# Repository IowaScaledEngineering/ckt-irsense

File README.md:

This is the software library, example applications, and hardware design files for the Iowa Scaled Engineering CKT-IRSENSE Reflective Infrared Proximity Sensor

The product can be found at:
http://www.iascaled.com/store/CKT-IRSENSE

Hardware use documentation (the manual) can be found in the /doc/ directory.

Like all public Iowa Scaled Engineering designs, the CKT-IRSENSE is both open hardware and open source software.  Please refer to the hardware and software license files in this repository for details.

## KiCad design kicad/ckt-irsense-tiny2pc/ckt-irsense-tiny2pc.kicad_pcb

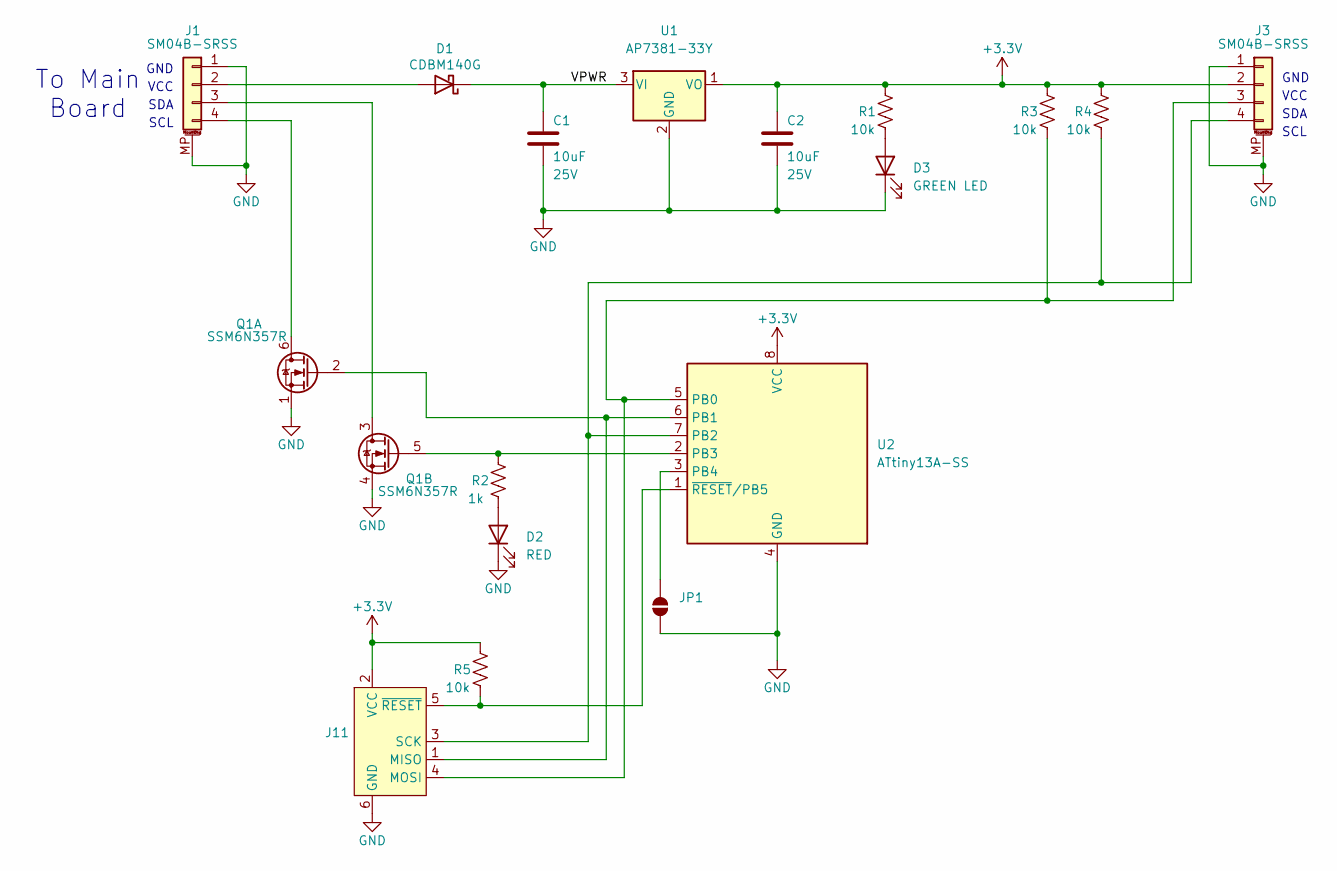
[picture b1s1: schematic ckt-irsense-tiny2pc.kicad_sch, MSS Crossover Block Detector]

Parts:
C1, C2: 10uF; C_0805_2012Metric; Voltage 25V
D1: CDBM140G; SOD-123T
D2: RED; LED_0805_2012Metric
D3: GREEN LED; LED_0805_2012Metric
J1, J3: SM04B-SRSS; JST_SH_SM04B-SRSS-TB_1x04-1MP_P1.00mm_Horizontal
J11: Conn_AVR_TagConnect_TC2030; Tag-Connect_TC2030-IDC-NL_2x03_P1.27mm_Vertical
JP1: SolderJumper_2_Open; SolderJumper-2_P1.3mm_Open_RoundedPad1.0x1.5mm
Q1: SSM6N357R; TSOP6F
R1, R3, R4, R5: 10k; R_0805_2012Metric
R2: 1k; R_0805_2012Metric
U1: AP7381-33Y; SOT-89-3
U2: ATtiny13A-SS; ATMEL_SO8_DUAL

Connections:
+3.3V: C2.1, J3.2, J11.2 (VCC), R1.2, R3.2, R4.2, R5.2, U1.1 (VO), U2.8 (VCC)
/VPWR: C1.1, D1.1 (K), U1.3 (VI)
GND: C1.2, C2.2, D2.1 (K), D3.1 (K), J1.1, J1.MP (MountPin), J3.1, J3.MP (MountPin), J11.6 (GND), JP1.1 (A), Q1.1 (S), Q1.4 (S), U1.2 (GND), U2.4 (GND)
unnamed: D1.2 (A), J1.2
unnamed: D2.2 (A), R2.1
unnamed: D3.2 (A), R1.1
unnamed: J1.3, Q1.3 (D)
unnamed: J1.4, Q1.6 (D)
unnamed: J11.1 (MISO), Q1.2 (G), U2.6 (PB1)
unnamed: J3.3, J11.4 (MOSI), R3.1, U2.5 (PB0)
unnamed: J3.4, J11.3 (SCK), R4.1, U2.7 (PB2)
unnamed: J11.5 (~RESET), R5.1, U2.1 (~RESET/PB5)
unnamed: JP1.2 (B), U2.3 (PB4)
unnamed: Q1.5 (G), R2.2, U2.2 (PB3)

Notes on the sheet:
GND
VCC
SCL
SDA
To Main Board

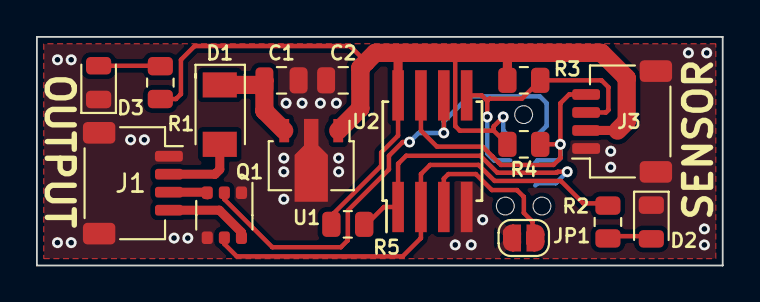
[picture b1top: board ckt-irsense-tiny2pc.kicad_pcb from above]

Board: 2 copper layers, 38.1 x 12.7 mm, 17 parts (1 on the bottom side), 14 nets.

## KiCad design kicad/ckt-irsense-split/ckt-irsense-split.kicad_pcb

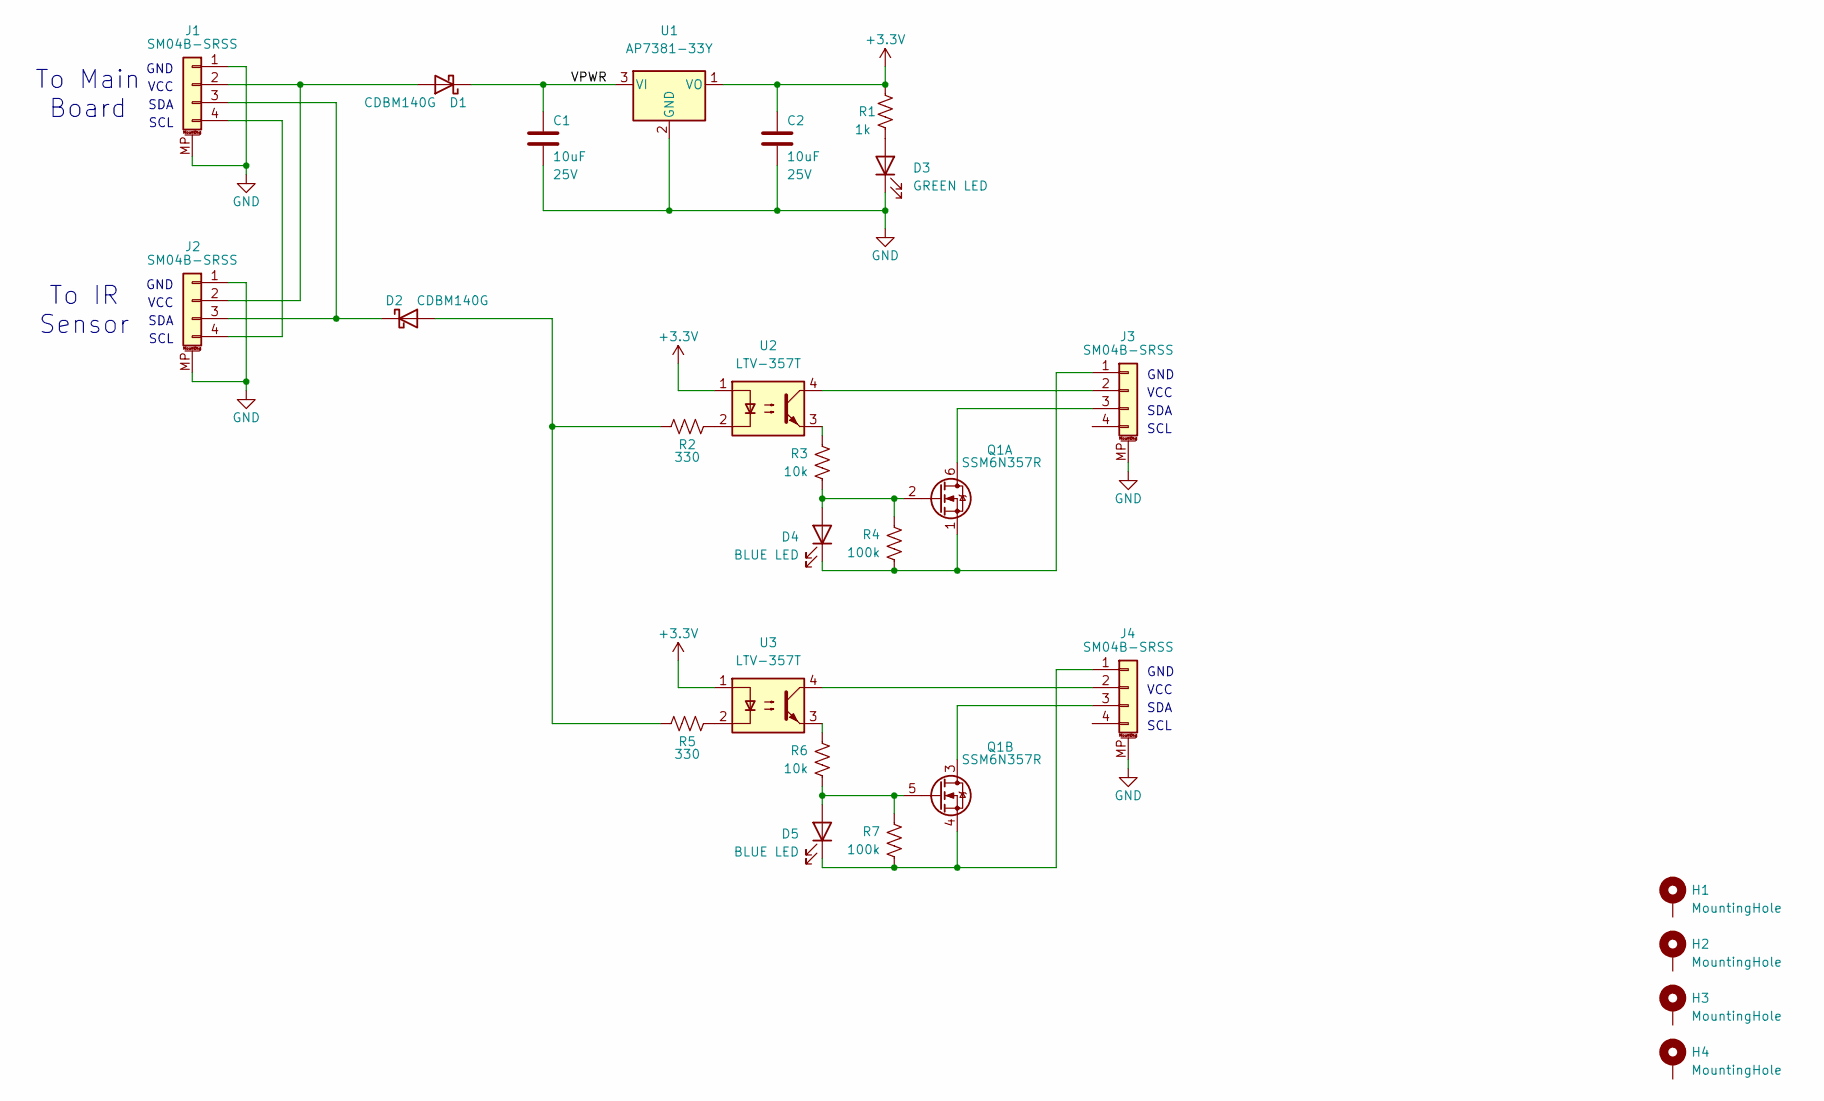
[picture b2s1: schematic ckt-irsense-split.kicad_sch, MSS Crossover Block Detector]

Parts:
C1, C2: 10uF; C_0805_2012Metric; Voltage 25V
D1, D2: CDBM140G; SOD-123T
D3: GREEN LED; LED_0805_2012Metric
D4, D5: BLUE LED; LED_0805_2012Metric
H1, H2, H3, H4: MountingHole; MountingHole_3.2mm_M3_Pad
J1, J2, J3, J4: SM04B-SRSS; JST_SH_SM04B-SRSS-TB_1x04-1MP_P1.00mm_Horizontal
Q1: SSM6N357R; TSOP6F
R1: 1k; R_0805_2012Metric
R2, R5: 330; R_0805_2012Metric
R3, R6: 10k; R_0805_2012Metric
R4, R7: 100k; R_0805_2012Metric
U1: AP7381-33Y; SOT-89-3
U2, U3: LTV-357T; SO-4_4.4x3.6mm_P2.54mm

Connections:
+3.3V: C2.1, R1.2, U1.1 (VO), U2.1, U3.1
/VPWR: C1.1, D1.1 (K), U1.3 (VI)
GND: C1.2, C2.2, D3.1 (K), J1.1, J1.MP (MountPin), J2.1, J2.MP (MountPin), J3.MP (MountPin), J4.MP (MountPin), U1.2 (GND)
unnamed: D1.2 (A), J1.2, J2.2
unnamed: D2.2 (A), R2.2, R5.2
unnamed: D2.1 (K), J1.3, J2.3
unnamed: D3.2 (A), R1.1
unnamed: D4.2 (A), Q1.2 (G), R3.1, R4.2
unnamed: D4.1 (K), J3.1, Q1.1 (S), R4.1
unnamed: D5.2 (A), Q1.5 (G), R6.1, R7.2
unnamed: D5.1 (K), J4.1, Q1.4 (S), R7.1
unnamed: J1.4, J2.4
unnamed: J3.2, U2.4
unnamed: J3.3, Q1.6 (D)
unnamed: J4.2, U3.4
unnamed: J4.3, Q1.3 (D)
unnamed: R2.1, U2.2
unnamed: R3.2, U2.3
unnamed: R5.1, U3.2
unnamed: R6.2, U3.3

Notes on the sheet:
SDA
GND
To IR Sensor
VCC
SCL
To Main Board

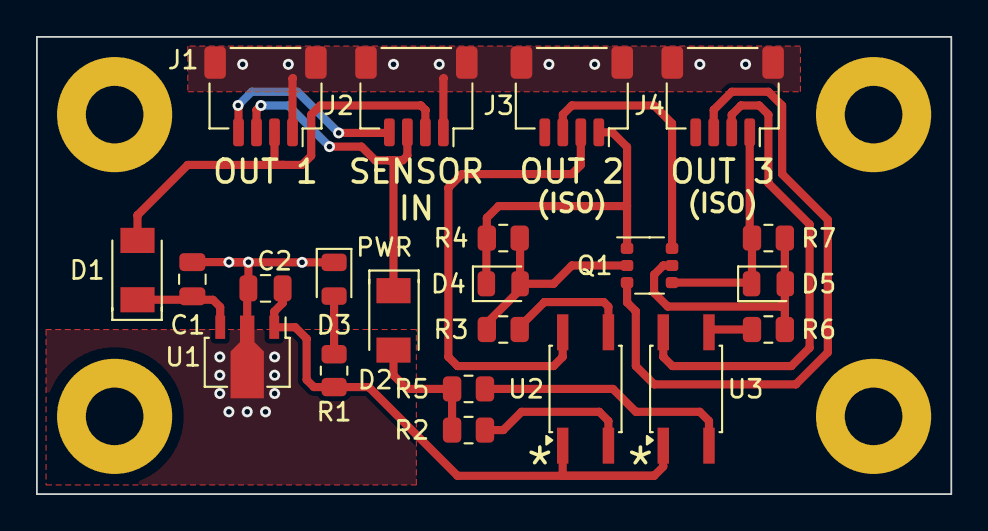
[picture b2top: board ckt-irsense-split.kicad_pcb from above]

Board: 2 copper layers, 50.8 x 25.4 mm, 26 parts (0 on the bottom side), 20 nets.

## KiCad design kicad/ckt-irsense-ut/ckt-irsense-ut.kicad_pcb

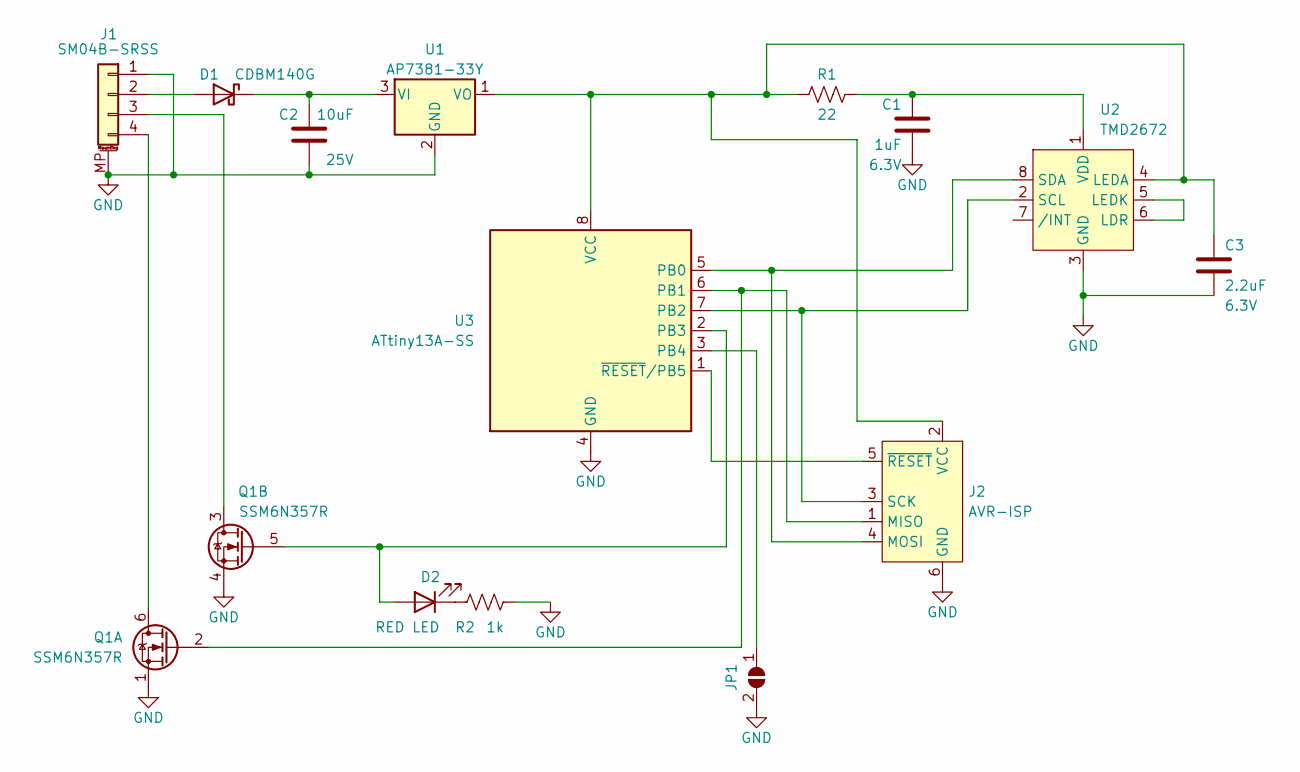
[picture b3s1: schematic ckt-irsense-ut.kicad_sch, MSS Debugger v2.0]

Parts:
C1: 1uF; C_0805_2012Metric; Voltage 6.3V
C2: 10uF; C_0805_2012Metric; Voltage 25V
C3: 2.2uF; C_0805_2012Metric; Voltage 6.3V
D1: CDBM140G; SOD-123T
D2: RED LED; LED_0805_2012Metric
J1: SM04B-SRSS; JST_SH_SM04B-SRSS-TB_1x04-1MP_P1.00mm_Horizontal
J2: AVR-ISP; Tag-Connect_TC2030-IDC-NL_2x03_P1.27mm_Vertical
JP1: SolderJumper_2_Open; SolderJumper-2_P1.3mm_Open_RoundedPad1.0x1.5mm
Q1: SSM6N357R; TSOP6F
R1: 22; R_0805_2012Metric
R2: 1k; R_0805_2012Metric
U1: AP7381-33Y; SOT-89-3
U2: TMD2672
U3: ATtiny13A-SS; SOIC-8_3.9x4.9mm_P1.27mm

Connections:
GND: C1.2, C2.2, C3.2, J1.1, J1.MP (MountPin), J2.6 (GND), JP1.2 (B), Q1.1 (S), Q1.4 (S), R2.1, U1.2 (GND), U2.3 (GND), U3.4 (GND)
unnamed: C1.1, R1.1, U2.1 (VDD)
unnamed: C2.1, D1.1 (K), U1.3 (VI)
unnamed: C3.1, J2.2 (VCC), R1.2, U1.1 (VO), U2.4 (LEDA), U3.8 (VCC)
unnamed: D1.2 (A), J1.2
unnamed: D2.1 (K), R2.2
unnamed: D2.2 (A), Q1.5 (G), U3.2 (PB3)
unnamed: J1.3, Q1.3 (D)
unnamed: J1.4, Q1.6 (D)
unnamed: J2.1 (MISO), Q1.2 (G), U3.6 (PB1)
unnamed: J2.3 (SCK), U2.2 (SCL), U3.7 (PB2)
unnamed: J2.4 (MOSI), U2.8 (SDA), U3.5 (PB0)
unnamed: J2.5 (~RESET), U3.1 (~RESET/PB5)
unnamed: JP1.1 (A), U3.3 (PB4)
unnamed: U2.5 (LEDK), U2.6 (LDR)

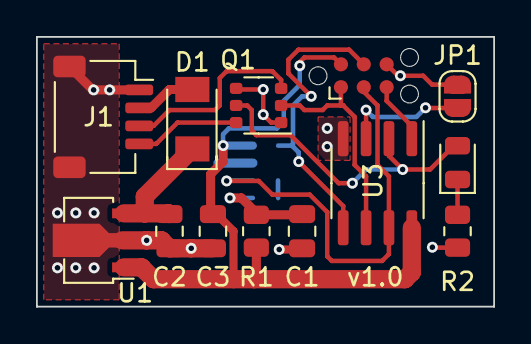
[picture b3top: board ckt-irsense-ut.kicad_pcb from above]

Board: 2 copper layers, 25.4 x 15.0 mm, 14 parts (1 on the bottom side), 15 nets.

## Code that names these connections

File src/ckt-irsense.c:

/*************************************************************************
Title:    IR reflective sensor v3.1
Authors:  Michael Petersen <railfan@drgw.net>
          Nathan D. Holmes <maverick@drgw.net>
File:     $Id: $
License:  GNU General Public License v3

LICENSE:
    Copyright (C) 2014 Michael Petersen & Nathan Holmes

    This program is free software; you can redistribute it and/or modify
    it under the terms of the GNU General Public License as published by
    the Free Software Foundation; either version 3 of the License, or
    any later version.

    This program is distributed in the hope that it will be useful,
    but WITHOUT ANY WARRANTY; without even the implied warranty of
    MERCHANTABILITY or FITNESS FOR A PARTICULAR PURPOSE.  See the
    GNU General Public License for more details.

*************************************************************************/

#include <stdlib.h>
#include <stdbool.h>
#include <avr/io.h>
#include <avr/interrupt.h>
#include <avr/wdt.h>
#include <util/delay.h>
#include <avr/eeprom.h>


#define   TMD267x1_ADDR   0x39
#define   INFO_ADDR       0x20

#define   PROXIMITY_THRESHOLD_DEFAULT     0x300
#define   SENSOR_ERROR_THRESHOLD  0
#define   PPULSE_DEFAULT          8

#define   ON_DEBOUNCE_DEFAULT   1

#define   SDA   PB0
#define   SCL   PB2

static inline void sda_low() { DDRB |= _BV(SDA); PORTB &= ~_BV(SDA); _delay_us(10); }
static inline void sda_high() { DDRB &= ~_BV(SDA); PORTB |= _BV(SDA); _delay_us(10); }
static inline void scl_low() { PORTB &= ~_BV(SCL); _delay_us(10); }
static inline void scl_high() { PORTB |= _BV(SCL); _delay_us(10); }

volatile uint8_t ticks;
volatile uint8_t decisecs = 0;

void initialize100HzTimer(void)
{
	// Set up timer 0 for 100Hz interrupts
	TCNT0 = 0;
	OCR0A = 94;  // 9.6MHz / 1024 / 94 = 100Hz
	ticks = 0;
	decisecs = 0;
	TCCR0A = _BV(WGM01);
	TCCR0B = _BV(CS02) | _BV(CS00);  // 1024 prescaler
	TIMSK0 |= _BV(OCIE0A);
}

ISR(TIM0_COMPA_vect)
{
	if (++ticks >= 10)
	{
		ticks = 0;
		decisecs++;
	}
}

void i2cStart(void)
{
	scl_high();
	sda_low();
	scl_low();
	sda_high();
}

void i2cStop(void)
{
	scl_low();
	sda_low();
	scl_high();
	sda_high();
}

uint8_t i2cWriteByte(uint8_t byte)
{
	uint8_t i = 0x80, ack;

	do
	{
		if(byte & i)
		{
			sda_high();
		}
		else
		{
			sda_low();
		}
		
		scl_high();
		scl_low();
		
		i >>= 1;
	} while(i);

	sda_high();  // Release SDA
	
	scl_high();
	if(PINB & _BV(SDA))
		ack = 0;
	else
		ack = 1;
	scl_low();

	return ack;
}

uint8_t i2cReadByte(uint8_t ack)
{
	uint8_t i, data = 0;

	for(i=0; i<8; i++)
	{
		data = data << 1;
		scl_high();
		if(PINB & _BV(SDA))
			data |= 0x01;
		scl_low();
	}
	
	if(ack)
		sda_low();
	scl_high();
	scl_low();
	sda_high();

	return data;
}

uint8_t writeByte(uint8_t addr, uint8_t cmd, uint16_t writeVal)
{
	uint8_t ack;
	
	i2cStart();
	
	i2cWriteByte(addr << 1);
	i2cWriteByte(cmd);
	ack = i2cWriteByte(writeVal);

	i2cStop();

	return ack;
}

uint8_t readWord(uint8_t addr, uint8_t cmd, uint16_t* data)
{
	uint8_t ack = 1;
	*data = 0xFFFF;
	
	i2cStart();
	
	ack &= i2cWriteByte(addr << 1);
	ack &= i2cWriteByte(cmd);

	i2cStart();

	ack &= i2cWriteByte((addr << 1) | 0x01);
	*data = i2cReadByte(1);
	*data |= ((uint16_t)i2cReadByte(0) << 8);
	
	i2cStop();

	return ack;
}

void init(void)
{
	MCUSR = 0;
	wdt_reset();
	wdt_enable(WDTO_250MS);
	wdt_reset();

	// Configure ADC
	ADMUX = 0x02;  // ref = VCC, right-justified, input = PB4 (ADC2)
	ADCSRA = 0x87; // ADC enabled, prescaler = 128
	DIDR0 = _BV(ADC2D);  // Disable ADC2 digital input buffer
	
	PORTB = _BV(SCL) | _BV(PB1);  // All outputs low except SCL and PB1
	DDRB |= _BV(PB1) | _BV(SCL) | _BV(PB3);
	
#ifndef TWOPIECE
	// Enable internal pull-up on ADJ pin
	DDRB &= ~_BV(PB4);
	PORTB |= _BV(PB4);
#endif
}

#define TMD26711_ID_VALUE 0x20
#define TMD26713_ID_VALUE 0x29
#define TMD26721_ID_VALUE 0x32
#define TMD26723_ID_VALUE 0x38

void initializeTMD267x1()
{
	uint16_t i=0;
	uint8_t isTMD2671x = 0;
	
	// Initialize TMD267x1 (bit 0x80 set to indicate command)
	writeByte(TMD267x1_ADDR, 0x80|0x00, 0x00);   // Start with everything disabled
	writeByte(TMD267x1_ADDR, 0x80|0x01, 0xFF);   // Minimum ATIME
	writeByte(TMD267x1_ADDR, 0x80|0x02, 0xFF);   // Maximum integration time
	writeByte(TMD267x1_ADDR, 0x80|0x03, 0xFF);   // Minimum wait time

	if (readWord(TMD267x1_ADDR, 0x80|0x20|0x12, &i))
	{
		if ((i & 0xFF) < TMD26721_ID_VALUE) // Also applies for TMD277xx, same IDs
			isTMD2671x = 1;
	}
	
	// Note: IRQ not currently used
	writeByte(TMD267x1_ADDR, 0x80|0x08, 0x00);   // Set interrupt low threshold to 0x0000
	writeByte(TMD267x1_ADDR, 0x80|0x09, 0x00);
	writeByte(TMD267x1_ADDR, 0x80|0x0A, 0x00);   // Set interrupt low threshold to 0x0300
	writeByte(TMD267x1_ADDR, 0x80|0x0B, 0x03);
	writeByte(TMD267x1_ADDR, 0x80|0x0C, 0x10);   // Single out-of-range cycle triggers interrupt

	writeByte(TMD267x1_ADDR, 0x80|0x0D, 0x00);   // Long wait disabled
	writeByte(TMD267x1_ADDR, 0x80|0x0E, PPULSE_DEFAULT); // Pulse count

	writeByte(TMD267x1_ADDR, 0x80|0x0F, isTMD2671x?0x20:0x28);   // 100% LED drive strength, Use channel 1 diode (ch 1 seems less sensitive to fluorescent light) - TMD26711
	writeByte(TMD267x1_ADDR, 0x80|0x00, 0x27);   // Power ON, Enable proximity, Enable proximity interrupt (not used currently)
}

void setOutputs(bool detect)
{
#ifdef DOUBLEOUTPUT
	// In this mode, both outputs are active if detection, inactive otherwise
	// Useful for MSS-type setups
	if(detect)
	{
		PORTB |= _BV(PB3) | _BV(PB1);
	}
	else
	{
		PORTB &= ~(_BV(PB3) | _BV(PB1));
	}

#elif defined PULSE_OUTPUT
	static bool prev_detect = false;
	if (prev_detect != detect)
	{
		if (prev_detect)
			PORTB |= _BV(PB1);
		else
			PORTB |= _BV(PB3);
	} else {
		PORTB &= ~(_BV(PB3) | _BV(PB1));
	}
	prev_detect = detect;

	
#else
	if(detect)
	{
		PORTB |= _BV(PB3);
		PORTB &= ~_BV(PB1);
	}
	else
	{
		PORTB &= ~_BV(PB3);
		PORTB |= _BV(PB1);
	}
#endif

}

int main(void)
{
#ifdef TWOPIECE
	//  Two Piece Specific Setup
	uint16_t proximity_threshold = PROXIMITY_THRESHOLD_DEFAULT;
	uint16_t count = 0;  // 256 decisecs * 60 (long delay mode) = 15360 max count
	int16_t on_debounce, off_debounce;  // Signed so the math for off_debounce doesn't wrap
#else
	//  One Piece Specific Setup
	uint16_t proximity_threshold = (eeprom_read_byte((const uint8_t *)0x00) << 8) + eeprom_read_byte((const uint8_t *)0x01);
	if(0xFFFF == proximity_threshold)
		proximity_threshold = PROXIMITY_THRESHOLD_DEFAULT;
	uint8_t count = 0;
	int8_t on_debounce, off_debounce;
#endif
	uint16_t proximity;
	bool detect = false;
	uint8_t sensorError = 0;
//	uint8_t ppulse;
	uint8_t ack;
	int16_t adc, adc_filt = 0;
	
	// Application initialization
	init();
	initialize100HzTimer();
	sei();

	initializeTMD267x1();


	while (1)
	{
		wdt_reset();

		if(decisecs >= 1)
		{
			decisecs = 0;
//			ppulse = PPULSE_DEFAULT;
//			writeByte(TMD267x1_ADDR, 0x80|0x0E, ppulse);

			// Read ADC
			ADCSRA |= _BV(ADSC);  // Trigger conversion
			while(ADCSRA & _BV(ADSC));
			adc = ADC;
			adc_filt = adc_filt + ((adc - adc_filt) / 4);

			on_debounce = ON_DEBOUNCE_DEFAULT;
#ifdef TWOPIECE
			off_debounce = ((1023 - adc_filt) - 100 + 2) / 4;  // Invert, shift, divide-by-4, round
			if(off_debounce < 1)
				off_debounce = 1;  // Limit to 1
#else
			off_debounce = (adc_filt > 512) ? 0 : RELEASE_DECISECS;
#endif

#ifdef LONG_DELAY
			off_debounce *= 64;
#endif
			// Telemetry
//			writeByte(INFO_ADDR, adc_filt >> 8, adc_filt & 0xFF);

			if (sensorError)
			{
				initializeTMD267x1();
			}	

			ack = readWord(TMD267x1_ADDR, 0x80|0x20|0x18, &proximity);  // Read data register (0x80 = command, 0x20 = auto-increment)

			if (!ack)
			{
				// Sensor's gone wonky, reset it and try again
				if (sensorError < 255)
					sensorError++;

				if (sensorError > SENSOR_ERROR_THRESHOLD)
				{
					detect = false;
					proximity = 0;
					count = 0;
					setOutputs(detect);
				}

				continue;

			} else {
				sensorError = 0;
			}

			if(!detect & (proximity >= proximity_threshold))
			{
				// ON debounce
				count++;
				if(count > on_debounce)
				{
					detect = true;
					count = 0;
				}
			}
			else if(!detect & (proximity < proximity_threshold))
			{
				count = 0;
			}

			else if(detect & (proximity < proximity_threshold))
			{
				// OFF debounce
				count++;
				if(count > off_debounce)
				{
					detect = false;
					count = 0;
				}
			}
			else if(detect & (proximity >= proximity_threshold))
			{
				count = 0;
			}
			setOutputs(detect);

		}

	}
}

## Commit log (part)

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2014-01-02 Initial cut of IR sensor stuff
2014-01-02 More updates, changed pin assignments
2014-01-02 Move pins around again, make work like schematic
2014-01-02 Not done yet, but betterish
2014-01-10 Change static text so I can name the part later
2014-01-10 Updated irsense schematic, hopefully ready to start on PCB except for programming header
2014-01-10 Add 5-turn trimmer footprint Update footprint on schematic
2014-01-20 First cut of irsense pcb that passes DRC
2014-01-20 Schematic updates to make the pcb go together right
2014-01-22 Cleanup and get ready to submit to oshpark for drc
2014-01-22 Update voltage on input cap
2014-01-22 Fix for J1 soldermask clearance
2014-01-22 Change attiny to wide tssop8 footprint
2014-01-22 Shrink soldermask on U5
2014-01-22 More updates - fix footprint for Vishay VSOP
2014-01-22 Fixes to the irsense PCB to get 6/6 DRC on new VSOP part Add text to output pins and + on diodes
2014-01-26 Initial draft of stupid light controller schematic
2014-02-23 No idea where my first pg went, but this should be identical
2014-03-21 Added inner VDD/GND layers
2014-03-21 Moved transmit diode line away from VSOP. Added GND shield on top layer between VSOP and transistor.
2014-03-21 Moved tx diode vdd closer to diode and away from VSOP. Added more GND shielding
2014-03-22 Minor tweaks to metal and silk
2014-03-22 OSHPark order on 3/22/2014
2014-05-12 Swapped IR diode and LED Added Q1 to cost sheet
2014-05-12 Added ATtiny45 and usbtiny
2014-05-24 36kHz version
2014-06-13 New version using integrated IR sensor module
2014-06-13 Switched to ATtiny45
2014-06-13 Miserable failure at reducing size... tired. Going to bed.
2014-06-13 Some compaction
2014-06-13 Shrinkage
2014-06-13 Beefed up sensor pad metal (adhesion)
2014-06-13 Minor tweaks
2014-06-14 Ready for PG
2014-06-14 Moved some text
2014-06-22 Wider connector footprint (50mil)
2014-06-22 Changed to local connector footprint
2014-06-22 Sent to OSH on 6/13/2014
2014-06-22 Changed 22uF cap from 16V to 6.3V
2014-06-24 Sent to OSH 6/23
2014-06-29 New code for v3.1
2014-06-30 Added ADC for PPULSE
2014-06-30 Was open when checked in last...
2014-06-30 A little cleanup
2014-07-22 Add usermanual shell
2014-07-27 OFF debounce programmable code
2014-07-27 Updated tables for variable delay
2014-07-28 Blah!
2014-07-28 Changed hole size, added more install text
2014-07-28 Updated manual
2014-07-28 Updated usermanual
2014-07-28 Changed blue color in wiring diagram
2014-07-28 Changed table inner line colors Re-added page numbers
2014-07-29 Added open hardware/software text, changed to a serif font, and did a bit of rearranging
2014-07-29 Added more diagrams. Added features
2014-07-29 Re-linked images Changed install pic to show ballast around sensor
2014-07-29 Resized board image to be real-size when booklet printed
2014-07-30 Added ties
2014-07-30 Added sense distances Updated applications
2014-07-30 Fixed hyperlinks
2014-07-31 Added relay application
2014-07-31 Small tweaks to the wording.
2014-08-01 Changed name
2014-08-01 Changed a word...
2014-08-01 Fixed release target
2014-08-01 Move MCUSR config to the front of init() Set WDTON fuse bit
2014-08-01 Released hex file
2014-08-01 Added production target
2014-08-03 Small edits
2014-08-03 Added bag top
2014-08-29 Updated manual with more apps
2014-08-30 Added descriptions for applications
2014-08-30 Bold text on relay Softened red color (added 32 green and blue)
2014-09-04 Remove TK's name
2014-09-26 Updated diagrams to show explicit wire connections
2014-09-26 Fixed spring switch diagram text
2014-09-26 Fixed spring switch diagram wire z-axis
2014-10-16 Extended sensor pads to edge of board
2014-10-16 Changed version text
2014-10-17 Extended sensor pads
2014-10-27 Added long delay option (minutes vs. seconds)
2014-11-06 Added 12V option to relay. Added Long Delay option
2014-11-06 Cleaned up 20s vs. 23s
2015-01-18 Changed to use diode #1
2015-01-18 Add boilerplate files
2015-01-20 Rearrange apps
2015-02-02 Panelized boards
2015-02-02 Added panel of boards. Renamed oshpark gerbers.
2015-02-14 Production firmware. Also modified Makefile to allow flashing either file.
2015-02-28 Add i2c-irsense - a modified version of the body that passes the I2C lines through so that multiple heads can be connected to one micro
2015-06-23 Modify i2c breakout for irsense
2015-06-24 Add first cut of a I2C-IRSENSE board
2015-07-02 Update bag top. Re-pointed links in manual to applications directory.
2015-07-28 Insert for product bags
2015-08-01 Final version
2015-08-16 Initial release
2015-08-17 Declare timer volatile. Added atomic accesses to timer. Added output pin access functions.
2015-10-16 New idea for the i2c-irsense
2015-10-16 Initial cut of a possible separate CKT-IRSENSE with sensor and base
2015-10-17 Fixed text alignment
2015-10-26 Update base to include 100k pot for delay adjust Update .gitignore to ignore intermediate gsch2pcb files
2015-10-26 Narrow the i2c-irsense board
2015-11-02 Move silk from off the holes
2015-11-02 PG out the i2c-irsense
2015-11-02 Add pg 1.0 of the irsense base unit
2015-11-27 Swap D and /D around
2015-12-02 Update version silk text
2016-01-11 Reduced solder paste for ATtiny
2016-01-12 Reduced solder paste on U2
2016-01-26 New irsense stalk with large pads for direct solder
2016-01-29 Test board
2016-01-30 Sent to fab 1/29/2016
2016-02-05 Add i2c-irsense v1.1
2016-03-08 Add preliminary error handling. Needs more thought tomorrow.
2016-03-08 Added error forgiveness
2016-03-09 Change threshold to 0. Quick in/out could POR the sensor but not re-initialize.
2016-05-10 ckt-irsense-base v1.1 pg
2016-08-02 Added 2pc
2016-12-06 Rotated sensors 90deg, added better pin 1 mark
2016-12-06 Rotated sensors 90deg, added better pin 1 mark, added vias in cutlines
2016-12-06 Changed rev to 1.2
2016-12-07 Changed to 12x panel
2016-12-10 Fixed overhang on outline layer
2016-12-10 Enlarged inter-board vias
2016-12-10 Fab'd 12/9/2016
2016-12-12 Enlarged and moved switches/LEDs to make testing easier.
2016-12-13 Sent to fab 12/12/2016
2017-03-07 Smaller paste on AVR
2017-06-26 New version of I2C stalk
2017-06-26 Added 2nd RJ9 footprint
2017-06-28 Cleaned up silk/outlines
2017-06-28 Finished cleaning up outline. Added part values instead of refdes.
2017-08-29 Update manual to include 2PC version
2017-09-01 Cleanup
2017-12-12 I2C version with SH connector (and panel)
2017-12-15 Application diagram
2018-01-03 Rounded outline around tabs
2018-01-03 Sent to fab 1/2/2018
2018-01-06 Schematic for Qwiic version
2018-01-06 Qwiic layout
2018-01-06 Added label to symbol
2018-01-25 Pulled pads for sensor head back 2mils
2018-01-29 Sent to fab v2.1
2018-04-24 Changed to iseavrprog. Updated lastest hex files.
2018-04-24 Added Qwiic connector
2018-04-27 Added anchor metal for Qwiic connector. LVS/DRC clean.
2018-04-29 Sent to fab 4/28/2018
2019-02-09 Changed to 4x gain for TMD26721
2019-02-09 Cleaned line endings
2019-02-17 Firmware for TMD26721
2019-07-14 New manual
2019-07-14 Updated bag insert
2019-07-14 PDF of manual
2019-07-14 Updated title and reformatted
2020-03-04 Changed logo to TrainSpotter
2020-03-13 Bracket STL/Gcode
2020-03-13 Added tabs
2020-03-13 Moved tabs to clear components near sides
2020-07-02 v4 Changes: Removed Rpack Added JP1 Removed 22uF regulator and AVR caps Changed sensor cap to 2.2uF Changed LED to 0805 Changed input diode to CDBM140G Added J2
2020-07-02 v4 layout
2020-07-02 Added polarity to LED
2020-07-02 Added copper to JST mounting pads, fixed some metal planes, added website.
2020-07-02 Panelized sensors
2020-07-04 Sent to fab 7/2
2020-07-04 Fixed formatting
2020-07-14 Code for v4
2020-07-15 Updated tester for v4 (and others using a similar non-Qwiic pinout)
2020-07-15 Added regulator
2020-07-17 Fixed title block (v3 -> v4)
2020-08-02 Version 4 with ATtiny13A
2020-08-02 Moved U2 text
2020-08-02 Panelized v4.1
2020-08-05 Right angle version
2020-08-05 Fixed text on back and added panel
2020-08-08 Added fixed 3s delay for 1pc version and options for 2pc.
2020-08-08 Disable internal pull-up on 2PC version
2020-08-20 Updated to TrainSpotter branding
2020-08-20 Added assembly marks to sns panel
2020-08-20 Sent to fab 8/19
2020-08-28 Updated release time section
2020-08-28 Changed to 5s release time
2020-09-15 ATtiny13 version
2020-09-15 Updated graphics
2020-09-18 Updated manual & files
2020-09-27 v2 of the ckt-irsense-base to convert to an attiny13a
2020-09-27 Move a few things around
2020-09-27 Fixed J2 GND text
2020-10-10 Something michael changed
2020-10-11 Added firmware snapshots
2020-10-14 base v2.0
2020-10-17 Cleaned up Makefile
2020-10-17 Put fuse target at end
2020-10-18 Sent to fab 10/2020
2020-10-18 Modified programmig script
2020-10-23 User manuals
2020-10-25 Added model # and other minor tweaks
2020-10-25 original insert images
2020-10-25 Adjusted color balance in Gimp -20 toward yellow
2020-10-25 Added notes, PDF, and "yellowed" images
2020-10-26 Moved insert files to directory
2020-10-26 Rearranged user manual files
2020-11-13 Updated programming order
2020-11-30 Added fab text
2020-12-01 Changed from -B32 to -B4
2020-12-01 Reverted to original images
2020-12-25 Added loop
2020-12-27 Sent to fab (additional notes)
2020-12-27 Enhanced programming script
2021-02-11 Add 2pc and 2pc-long hex and scripts
2021-02-20 Added 8' versions
2021-02-20 Improved wait code
2021-02-25 Fab files with fab text
2021-03-16 New insert cards
2021-10-01 Updated printing preferences
2021-10-17 Support for TMD26711
2021-10-27 Added 3x panel
2021-11-01 3x panel
2021-12-31 Added print settings
2022-04-07 Make automatic sensor switching
2022-04-07 Update main hex file to do auto-sensor switching
2022-04-08 Autosensor version
2022-04-08 Updated print settings
2022-04-08 Revert "Autosensor version"
    This reverts commit cf47d66cce6b40746298163e2152ecd4a5f0d1dd.
2022-04-08 Make the 2pc code fit with autodetect Does NOT include long delay, which does not fit
2022-05-10 Changed long delay multiplier from 60 to 64 to make fit in 2PC. Added EEPROM code for proximity threshold.
2022-05-12 Added 8S2 footprint and moved C2/prog header 10mils away (and associated wiring)
2022-05-12 Added web version of user manual.
2022-05-12 Created panelized version
2022-05-12 Renamed PCB panel to array
2022-05-12 Restored original panel
2022-05-12 Renamed template
2022-05-12 Added RA and BASE arrays
2022-05-12 Swapped template and pcb file
2022-05-15 Removed paste on fiducials
2022-05-15 Sent to fab 5/14/2022
2022-09-08 Updated to automatically search for device
2022-10-15 Pick and place files
2022-10-16 Update 2pc base to get rid of the RJ and go to discrete resistors
2022-10-16 Dropped in v3
2022-10-16 PG of ckt-irsense-array v4.2
2022-10-16 Fix a line that got deleted
2022-10-16 Re-imported board
2022-10-16 PG array of 2pc bases - v3.0
2023-01-06 Distance chart
2023-02-02 Fixed version number
2023-02-09 Reduced connector mounting pad solder paste
2023-02-09 Updated connector paste
2023-02-11 Removed pnp files
2023-03-17 Increased J2 paste from ~50% to 72.5%
2023-03-17 Gerber for increased paste
2023-06-15 Added continuous programming
2023-06-15 Updated to latest printer settings
2023-06-22 Added solid connector and full Qwiic footprint. Added dummy metal on rails. v4.2 -> v4.3
2023-06-22 Removed middle tab
2023-06-28 Sent to fab June 2023
2023-07-06 Updated printer settings
2023-07-24 Added solid connector and full Qwiic footprint. Removed middle tab Added dummy metal on rails. v4.2 -> v4.3
2023-07-24 Added no holes text on right side
2023-07-25 Added right side text
2023-07-25 Added solid bar and full-size connector
2024-01-22 Array version of i2c-irsense
2024-01-22 I2C-IRSENSE-ARRAY fab files
2024-01-22 Actual i2c-irsense-array fab files this time
2024-11-15 Add ability to have symmetric (double) outputs
2024-12-31 10s and double output helper files
2024-12-31 v4.4 Fixed connector metal Changed to TSOP6F footprint
2025-01-11 PG for v4.4 RA panel
2025-01-16 Removed gcode
2025-02-10 Multi-programming support
2025-02-10 v4.5: Fixed output line removed in v4.4
2025-02-10 v4.5 fab files
2025-02-22 First swag at CKT-IRSENSE-UT
2025-02-22 Update to add text
2025-03-21 Reverted release time back to 5s
2025-07-15 Add pulsed output mode

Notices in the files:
kicad/ckt-irsense-split/ckt-irsense-split.kicad_pcb:
www.iascaled.com ©2026
